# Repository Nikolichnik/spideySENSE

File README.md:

# spideySENSE
Upotrebom ultrazvučnog senzora za Arduino razvojnu platformu, ostvarujemo uvid u svet oko nas novim čulom.

<hr>

<p align="center">
  
</p>

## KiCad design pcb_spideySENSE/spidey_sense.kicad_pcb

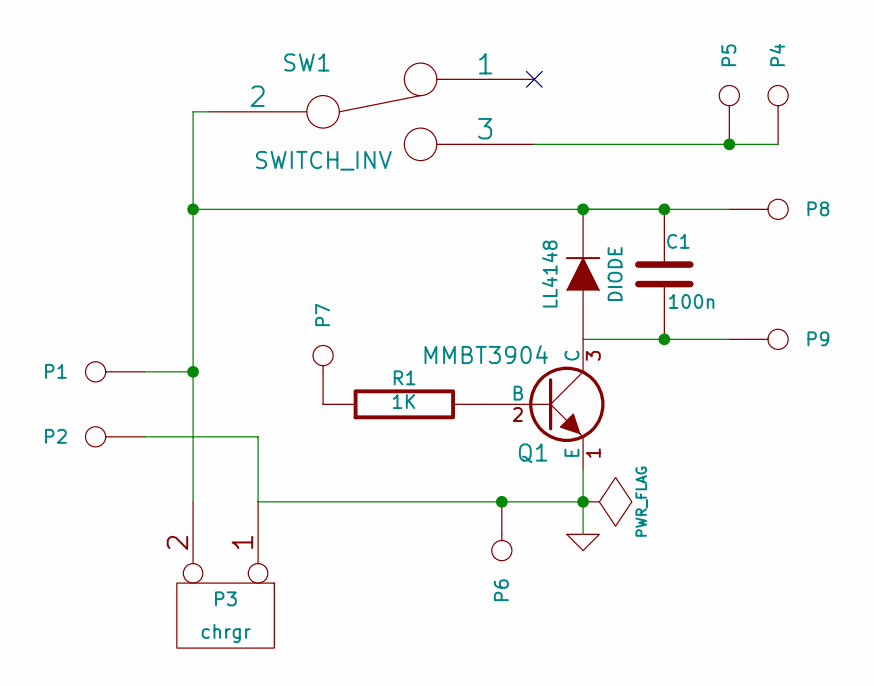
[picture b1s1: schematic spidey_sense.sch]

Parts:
C1: 100n
LL4148: DIODE
P1, P2, P4, P5, P6, P7, P8, P9: CONN_1
P3: chrgr
Q1: MMBT3904
R1: 1K
SW1: SWITCH_INV

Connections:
GND: P2.1, P3.1, P6.1, Q1.1 (E)
unnamed: C1.1, LL4148.2 (K), P1.1, P3.2 (PM), P8.1, SW1.2
unnamed: Q1.2 (B), R1.2
unnamed: P7.1, R1.1
unnamed: C1.2, LL4148.1 (A), P9.1, Q1.3 (C)
unnamed: P4.1, P5.1, SW1.3

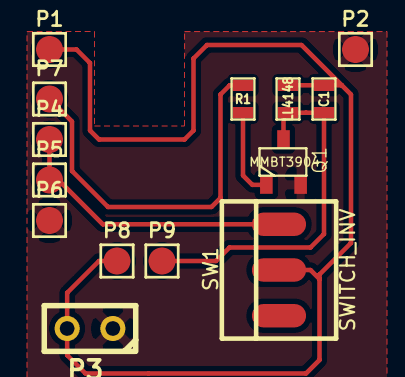
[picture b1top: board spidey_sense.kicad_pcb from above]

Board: 2 copper layers, 14 parts (0 on the bottom side), 6 nets.
